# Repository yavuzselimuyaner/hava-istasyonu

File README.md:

# Weather Station

**English** · [Türkçe](README.tr.md)

A device that measures outdoor temperature, humidity and pressure, publishes the readings to the internet over Wi-Fi, and shows them on a browser page.

## What we built

### 1. Two boards
| Main board (32x41 mm) | Sensor board (14x16 mm) |
|---|---|
|  |  |

- **Main board:** ESP32-C3 (Wi-Fi processor module), USB-C, 3.3 V regulator, reset and boot buttons, status LED, and a 4-pin connector for the sensor. Held in the enclosure with two M2 screws.
- **Sensor board:** BME280 (temperature, humidity, pressure) and a connector. It is separate from the main board and connected by a cable, because the processor and regulator warm up and a sensor next to them would read the temperature too high.
- **Design decisions:** The antenna extends past the board edge (the manufacturer's recommendation). Pull-up resistors were added to IO2 and IO8, which set the ESP32-C3's boot mode (found during the datasheet audit). The connector is right-angled, so the cable exits sideways and the enclosure stays low. The first three pins of the connector match the order of common 3-wire sensor modules (VCC, DATA, GND).
- **Tools:** Circuit described in Python with SKiDL and turned into a KiCad schematic ([main board](pcb/main/hava_sematik.pdf), [sensor board](pcb/sensor/hava_sematik.pdf)); each board is built in KiCad from its schematic's netlist, and copper traces are auto-routed with Freerouting. Result: electrical rules check (ERC) 0 errors, design rules check (DRC) 0 violations, schematic and board match.

### 2. Enclosure and radiation shield
- **Main enclosure (37x54x15 mm):** openings for USB-C, the cable exit, the buttons and the LED.
- **Radiation shield (60 mm diameter, 52 mm high):** three conical plates and a roof, so the sun does not heat the sensor while air still flows through. The sensor board hangs from the roof and the cable exits at the bottom.
- Generated by scripts in FreeCAD, with dimensions read directly from the board. A **collision check** was run by intersecting KiCad's per-part 3D board model with the enclosure: no collisions.

### 3. Firmware
C with ESP-IDF. Connects to Wi-Fi, reads the sensor, and publishes the reading as JSON over MQTT (WebSocket + TLS, port 443). The sensor can be the BME280 (main board) or, as an alternative, a DHT22. A BME280 driver, the measurement compensation math, and DHT22 decoding were written.

### 4. Web page
A single-file page (`web/index.html`) that subscribes to the same MQTT topic, shows temperature, humidity and pressure, and displays the weather service's value next to them for comparison.

### 5. How we tested it
- **Datasheet audit (3 rounds):** Pin and circuit details of every part were compared with the datasheets; the issues found (unconnected strapping pins, a missing capacitor) were fixed.
- **Tests on a PC:** The BME280 math was compared with Bosch's datasheet example and the reference formula; the BME280 driver was run against a virtual sensor; DHT22 decoding was tested with datasheet examples.
- **Simulation (Wokwi):** Since the simulator has no BME280, readings were taken with an ESP32-S3 and a virtual DHT22, published over MQTT, and seen on the web page. A negative temperature (−17.9 °C) and about 3 minutes of continuous operation were tested.
- **Process:** The design and code were generated with an LLM (Claude); every step was checked with the tests above, and the issues they found were fixed.
- **Limitation:** Not yet tested on real hardware.

## Folders
| Folder | Contents |
|---|---|
| `pcb/main`, `pcb/sensor` | Main board and sensor board (KiCad, generation scripts) |
| `case` | Enclosure and radiation shield (FreeCAD scripts, images) |
| `firmware` | ESP-IDF project and tests |
| `web` | Browser page |
| `docs` | Design documents (`tasarim/`: requirements, part selection, datasheet audits, pin table) and build instructions (`CALISTIRMA.md`), in Turkish |

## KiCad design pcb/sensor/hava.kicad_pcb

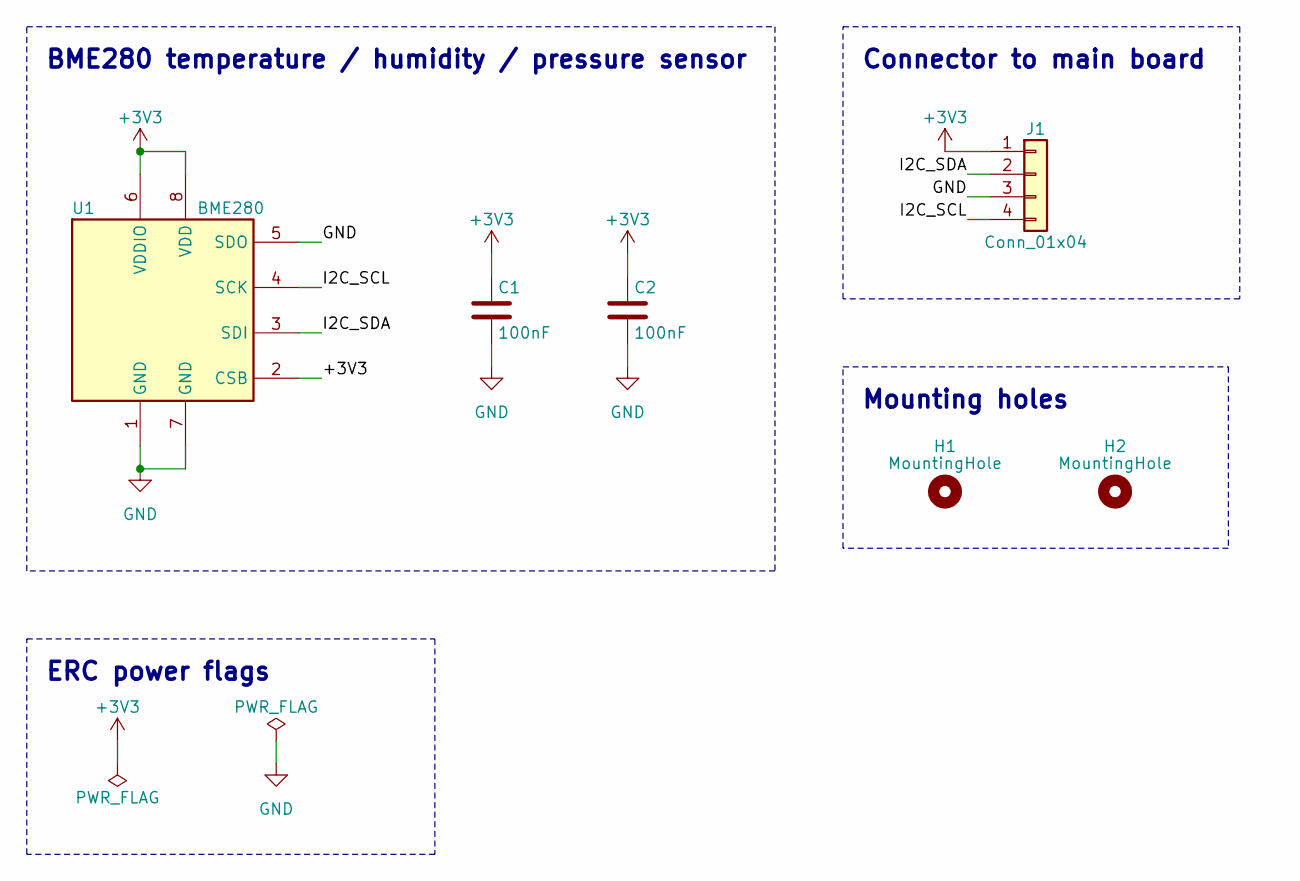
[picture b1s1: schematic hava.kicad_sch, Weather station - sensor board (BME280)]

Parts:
C1, C2: 100nF; C_0402_1005Metric
H1, H2: MountingHole; MountingHole_2.2mm_M2
J1: Conn_01x04; PinHeader_1x04_P2.54mm_Vertical
U1: BME280; Bosch_LGA-8_2.5x2.5mm_P0.65mm_ClockwisePinNumbering

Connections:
+3V3: C1.1, C2.1, J1.1, U1.2 (CSB), U1.6 (VDDIO), U1.8 (VDD)
/I2C_SCL: J1.4, U1.4 (SCK)
/I2C_SDA: J1.2, U1.3 (SDI)
GND: C1.2, C2.2, J1.3, U1.1 (GND), U1.5 (SDO), U1.7 (GND)

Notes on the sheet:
BME280 temperature / humidity / pressure sensor
ERC power flags
Connector to main board
Mounting holes

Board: 2 copper layers, 6 parts (0 on the bottom side), 4 nets, no tracks yet.

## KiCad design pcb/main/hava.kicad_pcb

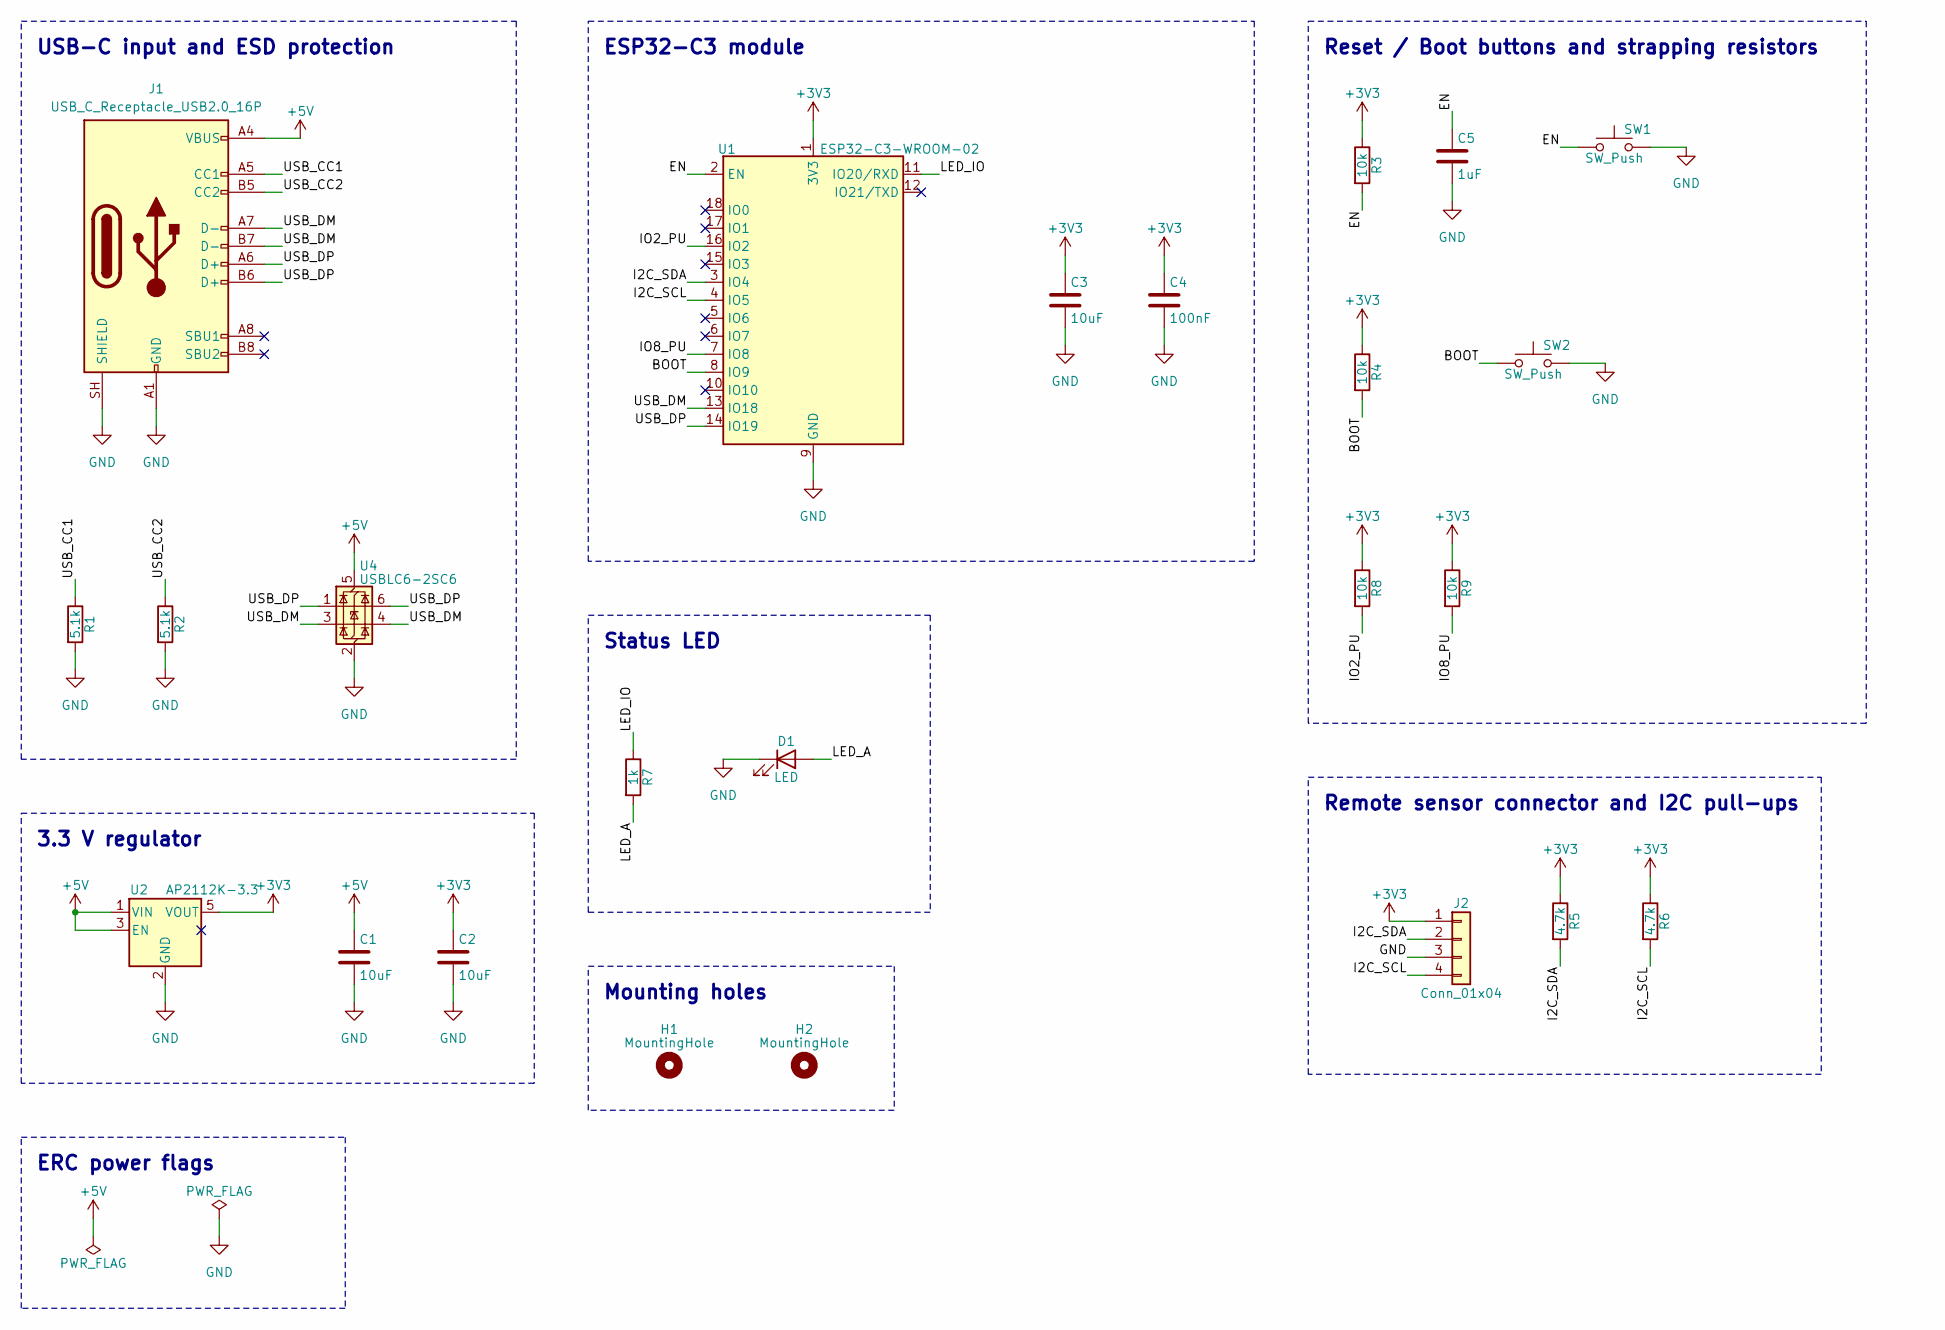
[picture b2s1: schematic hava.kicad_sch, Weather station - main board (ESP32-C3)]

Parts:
C1, C2, C3: 10uF; C_0805_2012Metric
C4: 100nF; C_0402_1005Metric
C5: 1uF; C_0402_1005Metric
D1: LED; LED_0603_1608Metric
H1, H2: MountingHole; MountingHole_2.2mm_M2
J1: USB_C_Receptacle_USB2.0_16P; USB_C_Receptacle_GCT_USB4105-xx-A_16P_TopMnt_Horizontal
J2: Conn_01x04; PinHeader_1x04_P2.54mm_Horizontal
R1, R2: 5.1k; R_0402_1005Metric
R3, R4, R8, R9: 10k; R_0402_1005Metric
R5, R6: 4.7k; R_0402_1005Metric
R7: 1k; R_0402_1005Metric
SW1, SW2: SW_Push; SW_SPST_B3U-1000P
U1: ESP32-C3-WROOM-02
U2: AP2112K-3.3; SOT-23-5
U4: USBLC6-2SC6; SOT-23-6

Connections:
+3V3: C2.1, C3.1, C4.1, J2.1, R3.1, R4.1, R5.1, R6.1, R8.1, R9.1, U1.1 (3V3), U2.5 (VOUT)
+5V: C1.1, J1.A4 (VBUS), J1.A9 (VBUS), J1.B4 (VBUS), J1.B9 (VBUS), U2.1 (VIN), U2.3 (EN), U4.5 (VBUS)
/BOOT: R4.2, SW2.1, U1.8 (IO9)
/EN: C5.1, R3.2, SW1.1, U1.2 (EN)
/I2C_SCL: J2.4, R6.2, U1.4 (IO5)
/I2C_SDA: J2.2, R5.2, U1.3 (IO4)
/IO2_PU: R8.2, U1.16 (IO2)
/IO8_PU: R9.2, U1.7 (IO8)
/LED_A: D1.2 (A), R7.2
/LED_IO: R7.1, U1.11 (IO20/RXD)
/USB_CC1: J1.A5 (CC1), R1.1
/USB_CC2: J1.B5 (CC2), R2.1
/USB_DM: J1.A7 (D-), J1.B7 (D-), U1.13 (IO18), U4.3 (I/O2), U4.4 (I/O2)
/USB_DP: J1.A6 (D+), J1.B6 (D+), U1.14 (IO19), U4.1 (I/O1), U4.6 (I/O1)
GND: C1.2, C2.2, C3.2, C4.2, C5.2, D1.1 (K), J1.A1 (GND), J1.A12 (GND), J1.B1 (GND), J1.B12 (GND), J1.SH (SHIELD), J2.3, R1.2, R2.2, SW1.2, SW2.2, U1.9 (GND), U1.19 (GND), U2.2 (GND), U4.2 (GND)

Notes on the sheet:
USB-C input and ESD protection
3.3 V regulator
ERC power flags
ESP32-C3 module
Status LED
Mounting holes
Reset / Boot buttons and strapping resistors
Remote sensor connector and I2C pull-ups

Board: 2 copper layers, 24 parts (0 on the bottom side), 15 nets, no tracks yet.

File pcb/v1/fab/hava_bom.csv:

Comment,Designator,Footprint,Quantity,LCSC Part #
10uF,"C1,C2,C3",C_0805_2012Metric,3,
100nF,"C4,C6",C_0402_1005Metric,2,
1uF,C5,C_0402_1005Metric,1,
LED,D1,LED_0603_1608Metric,1,
USB_C_Receptacle_USB2.0_16P,J1,USB_C_Receptacle_GCT_USB4105-xx-A_16P_TopMnt_Horizontal,1,
Conn_01x08,J2,PinHeader_1x08_P2.54mm_Vertical,1,
5.1k,"R1,R2",R_0402_1005Metric,2,
10k,"R3,R4",R_0402_1005Metric,2,
4.7k,"R5,R6",R_0402_1005Metric,2,
1k,R7,R_0402_1005Metric,1,
SW_Push,"SW1,SW2,SW3",SW_SPST_B3U-1000P,3,
ESP32-C3-WROOM-02,U1,ESP32-C3-WROOM-02,1,C2934560 (N4 surumu; dogrulanmadi)
AP2112K-3.3,U2,SOT-23-5,1,C51118 (AP2112K-3.3TRG1; dogrulanmadi)
BME280,U3,Bosch_LGA-8_2.5x2.5mm_P0.65mm_ClockwisePinNumbering,1,
USBLC6-2SC6,U4,SOT-23-6,1,

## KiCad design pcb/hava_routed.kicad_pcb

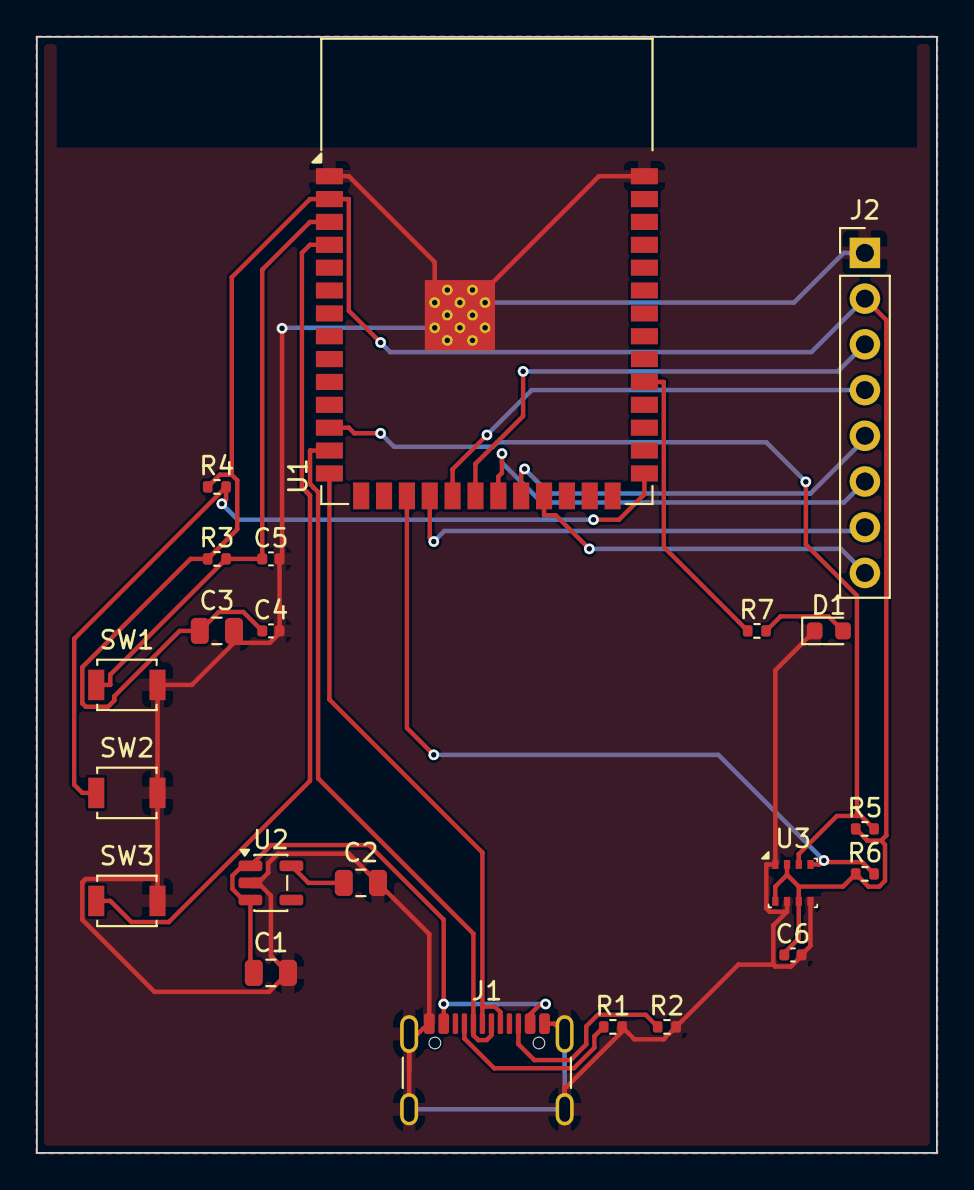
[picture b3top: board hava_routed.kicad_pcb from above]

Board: 2 copper layers, 50.0 x 62.0 mm, 22 parts (0 on the bottom side), 20 nets.

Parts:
C1, C2, C3: 10uF; C_0805_2012Metric
C4, C6: 100nF; C_0402_1005Metric
C5: 1uF; C_0402_1005Metric
D1: LED; LED_0603_1608Metric
J1: USB_C_Receptacle_USB2.0_16P; USB_C_Receptacle_GCT_USB4105-xx-A_16P_TopMnt_Horizontal
J2: Conn_01x08; PinHeader_1x08_P2.54mm_Vertical
R1, R2: 5.1k; R_0402_1005Metric
R3, R4: 10k; R_0402_1005Metric
R5, R6: 4.7k; R_0402_1005Metric
R7: 1k; R_0402_1005Metric
SW1, SW2, SW3: SW_Push; SW_SPST_B3U-1000P
U1: ESP32-S3-WROOM-1
U2: AP2112K-3.3; SOT-23-5
U3: BME280; Bosch_LGA-8_2.5x2.5mm_P0.65mm_ClockwisePinNumbering

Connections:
+3V3: C2.1, C3.1, C4.1, C6.1, J2.2, R3.1, R4.1, R5.1, R6.1, U1.2, U2.5, U3.2, U3.6, U3.8
+5V: C1.1, J1.A4, J1.A9, J1.B4, J1.B9, U2.1, U2.3
BOOT: R4.2, SW2.1, U1.27
BTN_IO: SW3.1, U1.4
EN: C5.1, R3.2, SW1.1, U1.3
GND: C1.2, C2.2, C3.2, C4.2, C5.2, C6.2, D1.1, J1.A1, J1.A12, J1.B1, J1.B12, J1.SH, J2.1, R1.2, R2.2, SW1.2, SW2.2, SW3.2, U1.1, U1.40, U1.41, U2.2, U3.1, U3.5, U3.7
I2C_SCL: R6.2, U1.17, U3.4
I2C_SDA: R5.2, U1.12, U3.3
LCD_BL: J2.8, U1.23
LCD_CS: J2.7, U1.18
LCD_DC: J2.6, U1.21
LCD_MOSI: J2.4, U1.19
LCD_RST: J2.5, U1.22
LCD_SCK: J2.3, U1.20
LED_IO: R7.1, U1.31
unnamed: J1.A5, R1.1
unnamed: J1.B5, R2.1
unnamed: D1.2, R7.2
USB_DM: J1.A7, J1.B7, U1.13
USB_DP: J1.A6, J1.B6, U1.14

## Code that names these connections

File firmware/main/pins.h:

#pragma once
/* docs/v1/02-denetim.md pin plani */
#define PIN_I2C_SDA   4
#define PIN_I2C_SCL   5
#define PIN_LCD_SCK   6
#define PIN_LCD_MOSI  7
#define PIN_LCD_DC    10
#define PIN_LCD_CS    3
#define PIN_LCD_RST   1
#define PIN_LCD_BL    0
#define PIN_LED       20
#define PIN_BUTTON    21
